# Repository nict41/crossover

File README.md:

# Variable Crossover — ESP Project 148

An EasyEDA-importable schematic for the **3-way state variable electronic
crossover** from Elliott Sound Products Project 148
(<https://sound-au.com/project148.htm>), redrawn from Figure 2.

Two cascaded 2nd-order state variable filters, 12 dB/octave, with continuously
variable crossover frequencies and adjustable Q. One channel — build two for
stereo.

Four variants are provided. They are the **same circuit** — identical filter
topology and identical signal connectivity, which the generator asserts on
every build — differing in the components that set the frequency range, in
whether the eight op-amp sections are packaged as four duals or two quads,
and in whether the board extras (volume controls, buffered outputs, muting)
are drawn:

| Variant | High/Mid | Mid/Low | Op-amps | File |
|---|---|---|---|---|
| Stock ESP P148 | 680 Hz – 4.8 kHz | 68 – 480 Hz | 4 × NE5532 dual | `esp-p148-3way-state-variable-crossover.json` |
| Retuned | 195 Hz – 1.03 kHz | 71 – 180 Hz | 4 × NE5532 dual | `esp-p148-3way-crossover-retuned-200hz-1khz.json` |
| Retuned, quad | 195 Hz – 1.03 kHz | 71 – 180 Hz | 2 × MC33079 quad | `esp-p148-3way-crossover-retuned-quad.json` |
| Retuned, quad, **SMD** | 195 Hz – 1.03 kHz | 73 – 186 Hz | 3 × MC33079 SOIC-14 | `esp-p148-3way-crossover-retuned-quad-smd.json` |

The **Retuned, quad** variant is electrically identical to the retuned one —
it just packs the same eight sections into two 14-pin quads instead of four
duals, which also halves the bypass caps (8 → 4). One quad per filter, so the
sections sharing a package are the ones already coupled by design.

The **SMD** variant is the one in `pcb/`, and it is not only a repackaging:
it adds a third quad (`U3`) for the output buffers, plus the volume controls,
the muting and the output DC blocking. That is why it lists three MC33079
where the through-hole quad variant lists two.

## Importing into EasyEDA

Everything here targets **EasyEDA Standard** (<https://easyeda.com/editor>) —
the generated JSON is Std's `docType: 3` PCB / `docType: 1` schematic format.
EasyEDA Pro can read it via **File → Import → EasyEDA Std**.

### The PCB (the finished, routed board)

1. Open <https://easyeda.com/editor> and go to **File → Open → EasyEDA…**
2. Choose `pcb/esp-p148-3way-crossover-retuned-quad-smd-pcb.json`.

It opens as a complete **four-layer** board: routed, with a solid ground
plane on Inner1 and a ground pour on the other three, and real LCSC part
numbers already attached to every assembled component. Nothing needs
assigning before you can look at it or order it — but do rebuild the copper
areas first, for the reason in the next section.

### The schematic

Same menu, then a `.json` from `schematic/` — one per variant. If your
editor build rejects it, try the matching `.legacy.json`: identical
drawing, older string-form document header.

Schematic symbols carry **generic** package names (`R_AXIAL-0.4`, `DIP-8`,
…), so the schematic on its own is not ready for layout — but you do not
need it to be, because the PCB above is already laid out. The two are
separate documents rather than one linked project, so EasyEDA will not
cross-check them; `gen_pcb_smd.py` does that instead, and asserts the
board's pads match the schematic's pins exactly on every run.

### What to check once it is open

The generator verifies its own geometry and `tools/validate_fab.py` checks
the file against EasyEDA's format and JLCPCB's limits, but a few things can
only be confirmed by a real import:

1. **Rebuild the copper areas** (right-click a pour → *Rebuild copper
   area*, or **Tools → Rebuild all copper areas**). Ground is a **plane**
   on this board, not a routed net — Inner1 is a solid ground plane, the
   other three layers are poured, and only
   a handful of short stubs are drawn as traces. This used to be optional
   insurance; it is now the thing that connects ground, so do it before
   the DRC below or the DRC will tell you ground is unconnected.
2. **Does the silkscreen appear?** This is the one known unknown. Our
   `TEXT` shapes are written without the pre-rendered glyph path that
   EasyEDA's own exports carry, relying on the editor to re-render from the
   text and size. Normal for generated files, expected to work, unverified
   here. If the designators and pin labels are missing, that is why.
3. **Design → Design Rule Check**, with JLCPCB's rule set. It should be
   clean; the repo's own checker already requires ≥ 8 mil clearance against
   JLCPCB's 5 mil limit.
4. **Look at the 3D view / photo view.** Part orientation is the usual
   failure mode for a hand-drawn footprint, and the SOIC-14's pin-1
   rotation against JLCPCB's convention is explicitly unconfirmed (see
   "Known limitations").
5. **Export Gerbers, BOM and CPL from EasyEDA**, not from this repo — see
   "Ordering" in `docs/pcb-notes-smd.md` for why the CPL here is reference
   only.

## Before you build this

Read [`docs/design-review.md`](docs/design-review.md). It lists the failure
modes that pass every automated check, marks which of them the board now
fixes, and keeps the reasoning for the ones it does — including why turn-on
transients from an active crossover are a tweeter problem specifically
(fixed: JFET muting with soft start), and why per-band volume knobs with no
master is the wrong control architecture for a preamp (fixed: `VR6`). What
is left is mostly mechanical: unverified hand-drawn footprints, and the
fact that nothing here has been built and measured.

## Repository layout

```
schematic/   EasyEDA schematics (.json + .legacy.json), one pair per variant,
             each with a matching .svg / .png preview
pcb/         the routed SMD board (+ .svg / .png preview)
docs/        circuit-notes.md      — how the circuit works, design equations
             pcb-notes-smd.md      — the board: layout, routing, verification
             design-review.md      — what could still go wrong
             panel-drilling.md     — GENERATED: front-panel hole positions
             parts.md              — GENERATED: the BOM, plus what you solder
             task-board.md         — open work, and what serialises
             decisions.md          — append-only log of what was measured
             subcircuits/          — GENERATED: one diagram per function block
             crossover-ranges.svg  — tuning-range diagram (+ .png)
             netlist.txt           — netlist extracted back out of the drawing
bom/         one bom-*.csv per variant, plus the JLCPCB BOM and CPL
tools/       gen_schematic.py     — generates the schematics
             gen_pcb_smd.py       — SMD PCB, routed + verified
             gen_range_diagram.py — generates the range diagram
             validate_fab.py      — EasyEDA import + JLCPCB limit checks
             find_board.py        — searches seeds/route orders for a clean board
             gen_spice.py         — SPICE deck, from the same netlist as the board
             run_sim.py           — runs the circuit-verification suite
             place.py / anneal.c / canneal.py   — the placement anneal
             router.c / croute.py               — the grid maze router
             geom.c  / cgeom.py                 — the exact-geometry checks
sim/         GENERATED: the ngspice deck (crossover.net, models.lib,
             jfet-*.lib). Analysis decks and their results are not committed.
```

`place.py`, `router.c` and `geom.c` each have a Python reference
implementation beside the compiled one (`PLACER=py`, `ROUTER=py`,
`CGEOM=py`), so every compiled path can be checked against readable code.

## Contributing (human or agent)

[`AGENTS.md`](AGENTS.md) is the one-page contract — it matters here more
than in most repositories, because almost everything in `schematic/`,
`pcb/`, `bom/`, `sim/` and several files in `docs/` is **generated**, and
editing the output instead of the generator is silently discarded.

```sh
python3 tools/check_all.py     # the gate: regenerate, verify, validate
```

Open work is in [`docs/task-board.md`](docs/task-board.md), marked by
whether it forces a board re-search (and so can only be done one at a
time). Measurements — kept *and* rejected — go in
[`docs/decisions.md`](docs/decisions.md).

## Regenerating

The schematic is generated, not hand-edited, so that the drawing and the netlist
can't drift apart:

```sh
python3 tools/gen_schematic.py      # schematics, previews, netlists, BOMs
python3 tools/gen_pcb_smd.py        # SMD board (routed; needs numpy)
python3 tools/gen_range_diagram.py  # docs/crossover-ranges.svg + .png
python3 tools/validate_fab.py --online   # EasyEDA import + JLCPCB limits
python3 tools/gen_spice.py && python3 tools/run_sim.py   # circuit simulation
```

`gen_spice.py` builds the ngspice deck from the **same netlist JSON the
board is built from**, so the thing that gets simulated cannot drift from
the thing that gets manufactured. `run_sim.py` then measures the crossover
points, the summed response, the DC at each output terminal, and the mute
chain. It needs `ngspice` (`apt install ngspice`).

`gen_pcb_smd.py` reads the netlist JSON that `gen_schematic.py` writes, so the
board cannot drift from the schematic — run them in that order.

Both need `cairosvg` for PNG output (`pip install cairosvg`); the SVGs are
written regardless.

The script places every component and wire on a 10 px grid, derives junction
dots from wire degree, then **re-extracts the netlist from the finished
geometry** and prints it. That extracted netlist is what's in `docs/netlist.txt`
— it is a check on the drawing, not a restatement of intent.

It builds every entry in `VARIANTS` and asserts that they all produce the same
netlist, so a retune that accidentally changed a connection would fail the
build rather than ship quietly.

## Circuit summary

Designators below are the **four-dual** drawing's. On the quad variants —
including the board — the same eight sections are U1A–D and U2A–D; that
mapping, and every part the board adds beyond the filter, is in
[`docs/circuit-notes.md`](docs/circuit-notes.md#function-blocks-on-the-smd-board).

| | Filter 1 | Filter 2 |
|---|---|---|
| Summing amp (high-pass out) | U1B → **HIGH** | U3A → **MID** |
| Integrator 1 (bandpass, feedback only) | U2A | U3B |
| Integrator 2 (low-pass out) | U2B → filter 2 | U4A → U4B → **LOW** |
| Frequency pot | VR1 (dual 20k) | VR2 (dual 20k) |
| Integrator caps | C1, C2 | C3, C4 |
| Q resistor | R3 = 12k | R13 = 12k |

Q = (5.6k + Rq) / (3 × Rq): 11k2 gives exactly 0.5 (Linkwitz-Riley), 11k gives
0.503, 12k gives 0.489, 5k04 gives Butterworth (Q = 0.707, 3 dB peak in the
summed response). The stock variant keeps the published 12k; the retuned
variant uses 11k, which is a stock value and four times closer to ideal.

The inverter U4B sits on the **bass** output rather than the midrange because
U3A, the input amplifier of the second filter, is already inverting.

TP1 and TP2 sum each filter's high-pass and low-pass outputs through 10 k
resistors; the signal nulls at the crossover frequency, so you can measure it
exactly with an oscillator. They're optional — the ESP PCB omits them.

### Tuning ranges

The retuned ranges don't overlap, but that is **not** what keeps the response
flat — separation is. Because the two filters are tuned independently, nothing
stops you setting them close together, and ranges that merely abut still meet
at the boundary:

| Range layout | Closest possible setting | Sum error there |
|---|---|---|
| Stock ESP P148 | 1.42 : 1 | −2.62 dB |
| Retuned | 1.08 : 1 | −3.57 dB |

The outputs never swap — filter 1 is unaware of filter 2, so HIGH is
unaffected. What collapses is MID, whose passband *is* the gap between the two
corners: squeeze that gap and it thins out, and the summed response develops a
broad suck-out. The degradation is gradual and already measurable at 1.6 : 1,
so the rule is **keep the two points at least 3 : 1 apart** (~1.5 octaves) for
under 1 dB. That's setting discipline, not something the hardware enforces —
note the stock ESP values have the same exposure. Nothing is damaged or
unstable; turn VR2 back down and it recovers. Full detail in
[`docs/circuit-notes.md`](docs/circuit-notes.md#setting-the-two-points-too-close-together).

### Frequency range

`f = 1/(2πRC)`, where R sweeps from the series resistor alone to series + 20 k
pot. The series resistor therefore sets both the top frequency *and* the
max/min ratio:

| Variant | R7, R8 | C1, C2 | High/Mid | R17, R18 | C3, C4 | Mid/Low |
|---|---|---|---|---|---|---|
| Stock | 3.3k | 10 nF | 683 Hz – 4.82 kHz | 3.3k | 100 nF | 68.3 – 482 Hz |
| Retuned | 4.7k | 33 nF | 195 Hz – 1.03 kHz | 13k | 68 nF | 70.9 – 180 Hz |

Nothing else differs — same Q, same op-amps, same 20 k pots. Larger series
resistors also load the previous stage *less*, so this direction is safe; the
article only warns against going below ~2.2k.

Full explanation, design equations and frequency tables: [`docs/circuit-notes.md`](docs/circuit-notes.md).

## Subcircuits

One diagram per functional block of the board, in
**[docs/subcircuits/](docs/subcircuits/README.md)**: input and master volume,
each of the two crossover filters, the level controls, the output buffers, the
two halves of the muting circuit, and power/decoupling.

They are **generated, not drawn**. `tools/gen_schematic.py` crops each block
out of the full sheet through the same `render_svg()` that renders the main
schematic, so the symbols, strokes and fonts are identical to it and cannot
drift. Rebuild them with:

```bash
python3 tools/gen_schematic.py
```

The part-by-part tables that go with the pictures are in
[docs/circuit-notes.md](docs/circuit-notes.md#function-blocks-on-the-smd-board).

## Additions to the original drawing

The ESP figures deliberately leave out supply wiring. This schematic adds it so
the netlist is complete:

* **J1** — ±15 V and ground input.
* **C5–C10** — 100 nF ceramic from each op-amp package's positive and negative
  supply pin to ground, as the article's text requires. Mount them right at
  the ICs; the board's placement search prices the distance directly.
* **C11, C12** — 10 µF bulk reservoir, one per rail.
* **R10/R11** and **R23/R24** — the unlabelled 10 k test-point resistors in
  Figure 2, given designators.

The `retuned-quad-smd` variant — the one the board is built from — adds more
still: a master volume, per-band volume trims, buffered outputs with DC
blocking and bleeders, and per-output muting with soft start. Every part and
what it does is listed in
[`docs/circuit-notes.md`](docs/circuit-notes.md#function-blocks-on-the-smd-board).

## Known limitations

### Of the schematics

These apply to the four `schematic/` variants. **None of them applies to the
routed board** — it has real footprints, real LCSC part numbers and a
verified layout; see the next list for its limitations.

* **Op-amps are drawn as separate sections** (U1A/U1B, U2A/U2B, …) rather than
  as multi-part components, so the BOM lists eight NE5532s where you only need
  four dual packages. Before PCB layout, merge each pair onto one DIP-8/SOIC-8
  part in EasyEDA. Supply pins 8 and 4 appear on the A section of each package
  only, which is the usual convention.
* **VR1 and VR2 are two dual-gang 20 k pots**, drawn as four gangs (VR1A, VR1B,
  VR2A, VR2B). Both gangs of a pot must track reasonably well.
* **VR3–VR6 are single-gang audio-taper pots** — three band trims and a
  master. They are passive attenuators, not part of any filter.
* **Footprints are placeholders** in the schematics. Assign real ones from the
  EasyEDA/LCSC library for your parts (axial vs. 0805, pot body, etc.).
* One deliberate wire crossing per filter, where the low-pass feedback rail
  crosses the high-pass rail. Crossings without a junction dot do not connect.

### Of the routed board

* **Nothing here has been built or measured.** It is verified against its own
  netlist, its own geometry, and — since the simulation work — its own
  behaviour in ngspice. All three are different claims from "it works on a
  bench".
* **The simulation cannot predict THD.** The op-amp is a behavioural
  macromodel with no device-level nonlinearity, so the distortion floor it
  reports is a measurement artefact. It is good for topology questions —
  does a device conduct when it should not, where do the crossover points
  land, what DC reaches the output — and useless for a distortion figure.
* **Winding both frequency knobs together collapses the mid band.** The
  two ranges deliberately do not overlap (73–186 Hz and 195 Hz–1.03 kHz),
  but they are *adjacent*: set both to the near end and the mid band is
  9 Hz wide, peaks 11.7 dB down, and the summed response has a 3.6 dB
  hole. Nothing prevents it and nothing on the panel warns about it —
  keep the two knobs apart.
* **Three footprints are hand-drawn and unconfirmed against a datasheet** —
  SOIC-14, the 10 µF electrolytic, and the dual-gang pot body. The pot's
  locating-boss holes are absent rather than guessed: a hole in the wrong
  place is a re-order, a missing one is a hand drill.
* **Whether the silkscreen renders after import is untested.** Our `TEXT`
  shapes carry no pre-rendered glyph path, which is normal for generated
  files and expected to work — but it is the one thing that cannot be
  checked without importing.
* **The board is past JLCPCB's 100 × 100 mm price tier** at 149.6 mm on its
  long side. That is set by the nine front-panel controls, not by routing:
  a control costs panel width whatever the router does.

## KiCad

`kicad/esp-p148-3way-crossover-retuned-quad-smd.kicad_sch` — the same
schematic as a **KiCad 8 schematic**, generated by `tools/gen_kicad.py`.
Open `kicad/crossover.kicad_pro`, or the `.kicad_sch` on its own.

It is **self-contained**: every symbol is embedded in the file's own
`lib_symbols`, one per component instance, so nothing needs to be
installed and no library path has to resolve. Nets are carried by labels
exactly as they are drawn.

It is not a second drawing of the circuit. `gen_kicad.py` reads the very
geometry `gen_schematic.py` lays out — every pin in absolute coordinates,
every wire polyline, every label — and translates it, so the two cannot
disagree about connectivity. And it checks: after emitting the file it
parses it back, rebuilds the netlist from the geometry alone, and refuses
to write anything unless that matches the schematic's own netlist.

`kicad/esp-p148-3way-crossover-retuned-quad-smd.kicad_pcb` — a **routing
seed**, for handing to an external router or placement tool. It is placed
but not wired:

* the committed outline at its real size, **149.6 × 63.5 mm**;
* the **edge components on the board** at their committed positions — the
  nine front-panel controls and the five rear connectors — because those
  are mechanical and not a router's to move;
* **every other part parked outside the outline** on a grid, to be placed;
* the full netlist on the pads, so there is a ratsnest to work from;
* the four mounting holes, so nothing routes through a screw;
* and **no tracks, no vias and no zones** — not even the ground pour this
  project otherwise treats as load-bearing.

It is read from the committed `pcb/*.json`, so it cannot describe a board
that was never built, and the emitted file is parsed back and checked
before it is written: bare of copper, every edge part inside the outline,
every other part clear of it, pad nets identical to the board's.

## PCB

### SMD board, routed, for JLCPCB fab + assembly

`pcb/esp-p148-3way-crossover-retuned-quad-smd-pcb.json` — **149.6 ×
63.5 mm**, **four layers**, **fully routed**, nine front-panel controls on
the board (a frequency pot and a volume trim per band, a master volume, and
a mute button per band), trace width matched to purpose (12 mil signal,
16 mil power/ground), 45° chamfered corners, every SMD part a real LCSC
line item.

The stackup is L1 signal / **L2 solid GND plane** / L3 signal / L4 signal.
Two layers could not route this board once the three panel mute buttons
went into the front row — see
[`docs/pcb-notes-smd.md`](docs/pcb-notes-smd.md#the-stackup).

Every part that reaches an edge is pinned into one of two rows — the panel
row on the front, the connector row on the back — and nothing may sit
outside either, so the board edges land 1.27 mm behind them. See
[Two pinned edge rows](docs/pcb-notes-smd.md#two-pinned-edge-rows).

Every SMD ground pad is **fanned out to the plane before any signal net is
routed** — a via on the pad, straight down. Repairing ground afterwards
does not work once the traces are down, and that is what used to leave
op-amp ground pins stranded.

Beyond the filter itself it carries buffered outputs with build-out
resistors, DC blocking and bleeders, a 47 kΩ line input, bulk and per-IC
supply decoupling, and **per-output muting with power-up soft start** — a
JFET shunting each buffer input, steering diodes so one button mutes one
band, and an RC that holds everything muted until the rails settle and
re-mutes fast when they collapse. The three mute buttons are **on the
board**, in the panel row beside the volume trims - right-angle push-lock
DPDTs, so their plungers come out of the board edge alongside the pot
shafts. `J6` carries only the optional panel LEDs, which light when a band
is playing. No audio leaves the board. Which parts do what, block
by block, is in
[`docs/circuit-notes.md`](docs/circuit-notes.md#function-blocks-on-the-smd-board).

```
board 149.6 x 63.5 mm | 86 footprints | 242 pads | 227 tracks | 159 vias
verified: all nets connected, all clearances >= 8 mil, no unrouted nets,
          pads match the schematic exactly
```

On the rear edge, left to right: **line input, LOW, MID, HIGH, power** —
the three outputs adjacent and in the same order as the front panel, with
the power block at the far end from the input so the two looms never run
together. On the front edge, left to right: MASTER,
**LOW mute**, LOW volume, MID/LOW frequency, **MID mute**, MID volume,
HIGH/MID frequency, **HIGH mute**, HIGH volume — nine controls, each mute
button beside the volume trim it mutes. The board lies **flat in the
enclosure, perpendicular to the front panel**, with right-angle pots and
right-angle switches on the front edge and their shafts and plungers
through the panel — the way a small amplifier board is usually arranged.
The frequency pots carry their sweep range on the silkscreen. The volume controls are single-gang
audio-taper pots (Alps RK097 pattern) wired as attenuators; the frequency
pots are the standard 9 mm dual-gang pattern. Both **need checking against
your parts' datasheets** — there are no locating-boss holes, deliberately;
see the notes.

**Drilling the panel:** [`docs/panel-drilling.md`](docs/panel-drilling.md)
is generated from the same placement as the copper, and gives the X of every
shaft and plunger from the board's left edge, the two pitches the row uses,
and where the four mounting holes actually ended up. Regenerate the board
and that file follows it, so it cannot drift from the part positions the way
a measured-off-the-preview drawing would.

Routing is checked by geometry that doesn't reuse the router's own bookkeeping:
exact pairwise clearance between every copper feature, union-find connectivity
per net, mounting-hole keepout, footprint-courtyard overlap, and pad-set
equality with the schematic. Those checks have caught real defects that would
otherwise have reached the fab, including a pre-existing footprint overlap
between two adjacent parts that nothing before the courtyard check could even
detect — see [`docs/pcb-notes-smd.md`](docs/pcb-notes-smd.md).

Part numbers were looked up live against the JLCPCB parts API; **re-check stock
before ordering**. Export Gerbers, BOM *and* CPL from EasyEDA rather than using
the CPL in this repo — a CPL's origin has to match the Gerbers, and only EasyEDA
knows that at export time.

JLCPCB won't assemble through-hole parts. **69 of the 86 footprints are
machine-placed**; the 17 you solder yourself are all through-hole and all of
them are edge or panel hardware:

* `VR1`–`VR6` — the six pots
* `SW1`–`SW3` — the three mute buttons
* `J1`–`J5` — power in, line in, and the three outputs
* `J6` — the optional panel-LED header
* `TP1`, `TP2` — the two test points

There is no off-board pot or switch wiring any more: every control is an
edge-mount part on the board itself.

## Getting the most out of it

The circuit is already lean, so build effort is easy to spend in the wrong
place. In order of what actually measures:

1. **Match within each filter.** The two integrator caps (C1/C2, C3/C4) and the
   two series resistors need to match *each other* — absolute value only sets
   the range. A mismatch acts exactly like pot mistracking, moving f0 and Q by
   its square root: 10 % costs −0.41 dB, 20 % costs −0.79 dB. Use 1 % resistors
   and matched caps; 5 % is fine everywhere else.
2. **Buy pot tracking, not exotic op-amps.** Same maths applies to the two
   gangs. And don't fit log-taper pots for a more even frequency scale — their
   gang tracking is much worse, and it lands straight on Q.
3. **Q resistor 11k, not 12k** — already done in the retuned variant. Free.
4. **Two quads instead of four duals** — shipped as the `retuned-quad`
   variant. The circuit splits perfectly at the filter boundary, four sections
   each, so one quad per filter: half the ICs, half the bypass caps, smaller
   board, no circuit change. Drawn with the MC33079 (closest in character to
   the NE5532); any standard quad pinout drops in — OPA1644, OPA4134,
   LME49740, TL074.

Things that look like simplifications but aren't: the input buffer U1A keeps
source impedance out of the Q and gain; the integrators have no DC feedback of
their own, so the state-variable loop must stay intact. Detail in
[`docs/circuit-notes.md`](docs/circuit-notes.md#where-accuracy-actually-pays).

## Building notes

* NE5532 is what the article specifies, for noise. Any decent audio dual op-amp
  will work.
* The 5.6 k resistors were 10 k in earlier versions of the article; 5.6 k was
  chosen to reduce thermal noise. Anything up to 10 k is fine, above that isn't
  recommended.
* To move a frequency range, change the integrator capacitors — smaller caps
  give a higher range. 4.7 nF in filter 1 gives roughly 1.45 kHz – 10 kHz.
  Watch that a test tweeter isn't driven below its rated minimum frequency.

## Credit and licence

Circuit design © Rod Elliott, Elliott Sound Products, Project 148 (2014).
The ESP article grants personal use and one printed copy for reference while
building; commercial use needs Rod Elliott's written permission. This repository
holds a re-drawn schematic for personal construction — please read the article
itself, and buy the ESP PCB if you want one.

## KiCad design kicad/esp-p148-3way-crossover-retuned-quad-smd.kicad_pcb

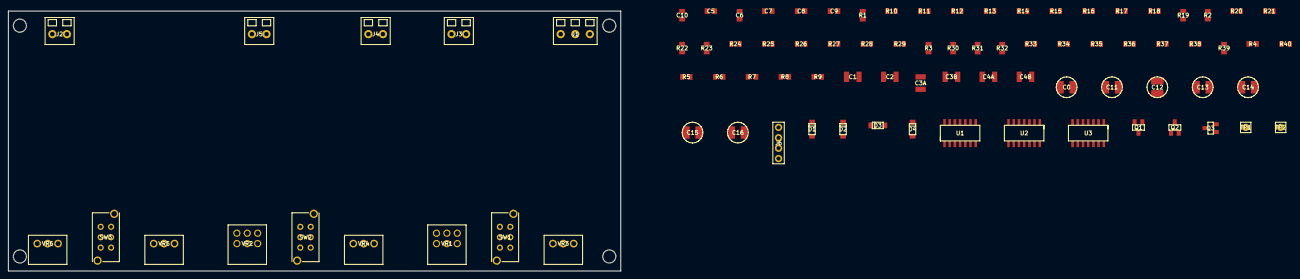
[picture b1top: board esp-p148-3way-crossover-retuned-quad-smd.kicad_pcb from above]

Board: 4 copper layers, 149.6 x 63.5 mm, 90 parts (0 on the bottom side), 58 nets, no tracks yet.

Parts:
C0, C11, C12, C13, C14, C15, C16: 10uF; CASE-D5xL5.4
C1, C2, C3A, C3B, C4A, C4B: 33nF; 1210
C5, C6, C7, C8, C9, C10: 100nF; 0805
D1, D2, D3, D4: 1N4148W; SOD-123
H1, H2, H3, H4: MountingHole
J1: TB-3P-3.5
J2, J3, J4, J5: TB-2P-3.5
J6: MUTE; HDR-1X4
Q1, Q2, Q3: MMBFJ112; SOT-23
R1: 47k; 0805
R2, R4, R5, R6, R12, R14, R15, R16, R20, R21: 5.6k; 0805
R3, R13: 11k; 0805
R7, R8: 4.7k; 0805
R9, R19, R22, R25, R26, R27: 100R; 0805
R10, R11, R23, R24, R31, R32, R33: 10k; 0805
R17, R18: 13k; 0805
R28, R29, R30: 100k; 0805
R34, R35, R36, R40: 1M; 0805
R37, R38, R39: 2.2k; 0805
SW1, SW2, SW3: DPDT LOCK; SW-PS22E05
TP1: TP1; THT-PAD
TP2: TP2; THT-PAD
U1, U2, U3: MC33079; SOIC-14
VR1, VR2: 20k dual; POT-9MM-DUAL
VR3, VR4, VR5: 10k log; POT-9MM-SINGLE
VR6: 50k log; POT-9MM-SINGLE

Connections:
+15V: C5.1, C7.1, C9.1, C11.1, J1.1, R37.1, R38.1, R39.1, U1.4, U2.4, U3.4
-15V: C6.2, C8.2, C10.2, C12.2, D4.1, J1.3, R34.2, R35.2, R36.2, R40.1, U1.11, U2.11, U3.11
GND: C5.2, C6.1, C7.2, C8.1, C9.2, C10.1, C11.2, C12.1, C16.2, J1.2, J2.2, J3.2, J4.2, J5.2, J6.4, Q1.2, Q2.2, Q3.2, R1.2, R3.2, R13.2, R28.2, R29.2, R30.2, SW1.1, SW1.7, SW1.8, SW2.1, SW2.7, SW2.8, SW3.1, SW3.7, SW3.8, U1.10, U1.12, U2.5, U2.10, U2.12, U3.12, VR3.3, VR4.3, VR5.3, VR6.3
HIGH: C13.2, J3.1, R28.1
HIGH_MUTE: Q1.1, R31.2, U3.3
HIGH_PRE: R9.2, VR3.1
HIGH_VOL: R31.1, VR3.2
INPUT: C0.1, VR6.2
INPUT_PRE: J2.1, VR6.1
LD1: J6.1, SW1.6
LD2: J6.2, SW2.6
LD3: J6.3, SW3.6
LOW: C15.2, J5.1, R30.1
LOW_MUTE: Q3.1, R33.2, U3.10
LOW_PRE: R22.2, VR5.1
LOW_VOL: R33.1, VR5.2
LP1: C2.2, R6.2, R11.1, R15.1, U1.14
LX1: R37.2, SW1.3
LX2: R38.2, SW2.3
LX3: R39.2, SW3.3
MG1: D1.2, Q1.3, R34.1, SW1.4
MG2: D2.2, Q2.3, R35.1, SW2.4
MG3: D3.2, Q3.3, R36.1, SW3.4
MID: C14.2, J4.1, R29.1
MID_MUTE: Q2.1, R32.2, U3.5
MID_PRE: R19.2, VR4.1
MID_VOL: R32.1, VR4.2
MUTE_SS: C16.1, D1.1, D2.1, D3.1, D4.2, R40.2
N160_280: C0.2, R1.1, U1.3
N350_300: R2.1, U1.1, U1.2
N530_100: R2.2, R5.1, R6.1, U1.6
N530_700: R12.1, R15.2, R16.1, U2.2
N570_320: R3.1, R4.1, U1.5
N570_920: R13.1, R14.1, U2.3
N680_300: R5.2, R9.1, R10.2, U1.7, VR1.1
N680_900: R16.2, R19.1, R23.2, U2.1, VR2.1
N830_300: R7.1, VR1.2, VR1.3
N830_900: R17.1, VR2.2, VR2.3
N950_300: C1.1, R7.2, U1.9
N950_900: C3A.1, C3B.1, R17.2, U2.6
N1100_300: C1.2, R4.2, U1.8, VR1.1
N1100_900: C3A.2, C3B.2, R14.2, U2.7, VR2.1
N1280_300: R8.1, VR1.2, VR1.3
N1280_900: R18.1, VR2.2, VR2.3
N1400_300: C2.1, R8.2, U1.13
N1400_900: C4A.1, C4B.1, R18.2, U2.9
N1580_640: C4A.2, C4B.2, R12.2, R20.1, R24.1, U2.8
N1680_900: R20.2, R21.1, U2.13
N1850_900: R21.2, R22.1, U2.14
N2150_1250: R25.1, U3.1, U3.2
N2150_1400: R26.1, U3.6, U3.7
N2150_1550: R27.1, U3.8, U3.9
N2150_1700: U3.13, U3.14
N2260_1250: C13.1, R25.2
N2260_1400: C14.1, R26.2
N2260_1550: C15.1, R27.2
TP1: R10.1, R11.2, TP1.1
TP2: R23.1, R24.2, TP2.1

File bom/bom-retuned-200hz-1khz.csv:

Qty,Value,Package,Designators,Notes
1,10uF,C_AXIAL-0.2,"C0",""
2,33nF,C_AXIAL-0.2,"C1, C2",""
2,68nF,C_AXIAL-0.2,"C3, C4",""
8,100nF,C_AXIAL-0.2,"C5, C6, C7, C8, C9, C10, C11, C12",""
8,NE5532,DIP-8,"U1A, U1B, U2A, U2B, U3A, U3B, U4A, U4B","4 x dual op-amp packages (U1-U4); each drawn as two sections"
4,20k,POT-9MM-DUAL,"VR1A, VR1B, VR2A, VR2B","2 x dual-gang 20k linear pots (VR1, VR2); wired as rheostats"
1,47k,R_AXIAL-0.4,"R1","Sets the board's input impedance - see docs/design-review.md"
10,5.6k,R_AXIAL-0.4,"R2, R4, R5, R6, R12, R14, R15, R16, R20, R21",""
2,11k,R_AXIAL-0.4,"R3, R13","Sets filter Q (0.503); 11k2 = exact Q 0.5, 5k04 = Butterworth"
2,4.7k,R_AXIAL-0.4,"R7, R8",""
3,100R,R_AXIAL-0.4,"R9, R19, R22","Build-out resistors: R9/R19/R22 from each filter into its volume pot, R25/R26/R27 from each output buffer into the interconnect"
4,10k,R_AXIAL-0.4,"R10, R11, R23, R24","R10/R11/R23/R24 are the TP1/TP2 null network - optional"
2,13k,R_AXIAL-0.4,"R17, R18",""
1,IN,TB-2P-5.08,"J2","Signal input"
1,HIGH,TB-2P-5.08,"J3","Output terminal block to the treble amplifier"
1,MID,TB-2P-5.08,"J4","Output terminal block to the midrange amplifier"
1,LOW,TB-2P-5.08,"J5","Output terminal block to the bass amplifier"
1,PWR,TB-3P-5.08,"J1",""
2,TP,TESTPOINT,"TP1, TP2","Test points - optional, omit with R10/R11 and R23/R24"

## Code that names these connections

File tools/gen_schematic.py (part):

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    w((1680, 140 + OY), (1720, 140 + OY))
    resistor("R19", "100R", 1750, 140 + OY)
    w((1780, 140 + OY), (1820, 140 + OY))
    netlabel("MID" + vsuf, 1820, 140 + OY, anchor="start", dx=4, dy=3)

    # output inverter U4B (bass output; U3A already inverts the midrange)
    w((1580, 300 + OY), (1620, 300 + OY))
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    # buffer, and the pot's wiper becomes INPUT.  Same _PRE convention the
    # band volume pots use, so signal_map() folds it out and every variant
    # still has to agree about where the filter's input actually lands.
    netlabel("INPUT_PRE" if cfg.get("master_vol") else "INPUT",
             1130, 1260, anchor="start", dx=4, dy=3)
    w((1070, 1290), (1130, 1290))
    gnd(1130, 1290)
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        # same family but the wrong track.  VR3-VR5 really are 10k.
        pot("VR6", "50k log", mx, 1260, package="RK097-AUDIO-50K")
        w((mx - 30, 1260), (mx - 70, 1260))
        netlabel("INPUT_PRE", mx - 70, 1260, anchor="end", dx=-4, dy=3)
        w((mx + 30, 1260), (mx + 70, 1260))
        gnd(mx + 70, 1260)
        w((mx, 1290), (mx, 1320))
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            diode("D%d" % (1 + k), "1N4148W", cx - 70, my - 90)
            w((cx - 40, my - 90), (cx, my - 90))
            w((cx - 100, my - 90), (cx - 140, my - 90))
            netlabel("MUTE_SS", cx - 140, my - 90, anchor="end", dx=-4, dy=3)
            # Panel LED feed.  The resistor sets the current; the switch's
            # second pole (below) does the switching, so what leaves the
            # board on LD%d is a current-limited feed that is live only
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        resistor("R40", "1M", sx, my - 130, vertical=True)
        w((sx, my - 100), (sx, my - 90))
        w((sx, my - 90), (sx + 60, my - 90))
        netlabel("MUTE_SS", sx + 60, my - 90, anchor="start", dx=4, dy=3)
        w((sx, my - 90), (sx, my - 60))
        capacitor("C16", "10uF", sx, my - 30, vertical=True, polar=True,
                  label_side=-1, package="CASE-D5xL5.4")
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#  junctions, netlist extraction, output
# ==========================================================================
def split_wires():
    """Insert a real vertex wherever a wire end or pin dot lands mid-segment.

    EasyEDA joins a wire whose endpoint touches another wire, but the junction
    dot is only drawn where segments actually meet, so promote every such touch
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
